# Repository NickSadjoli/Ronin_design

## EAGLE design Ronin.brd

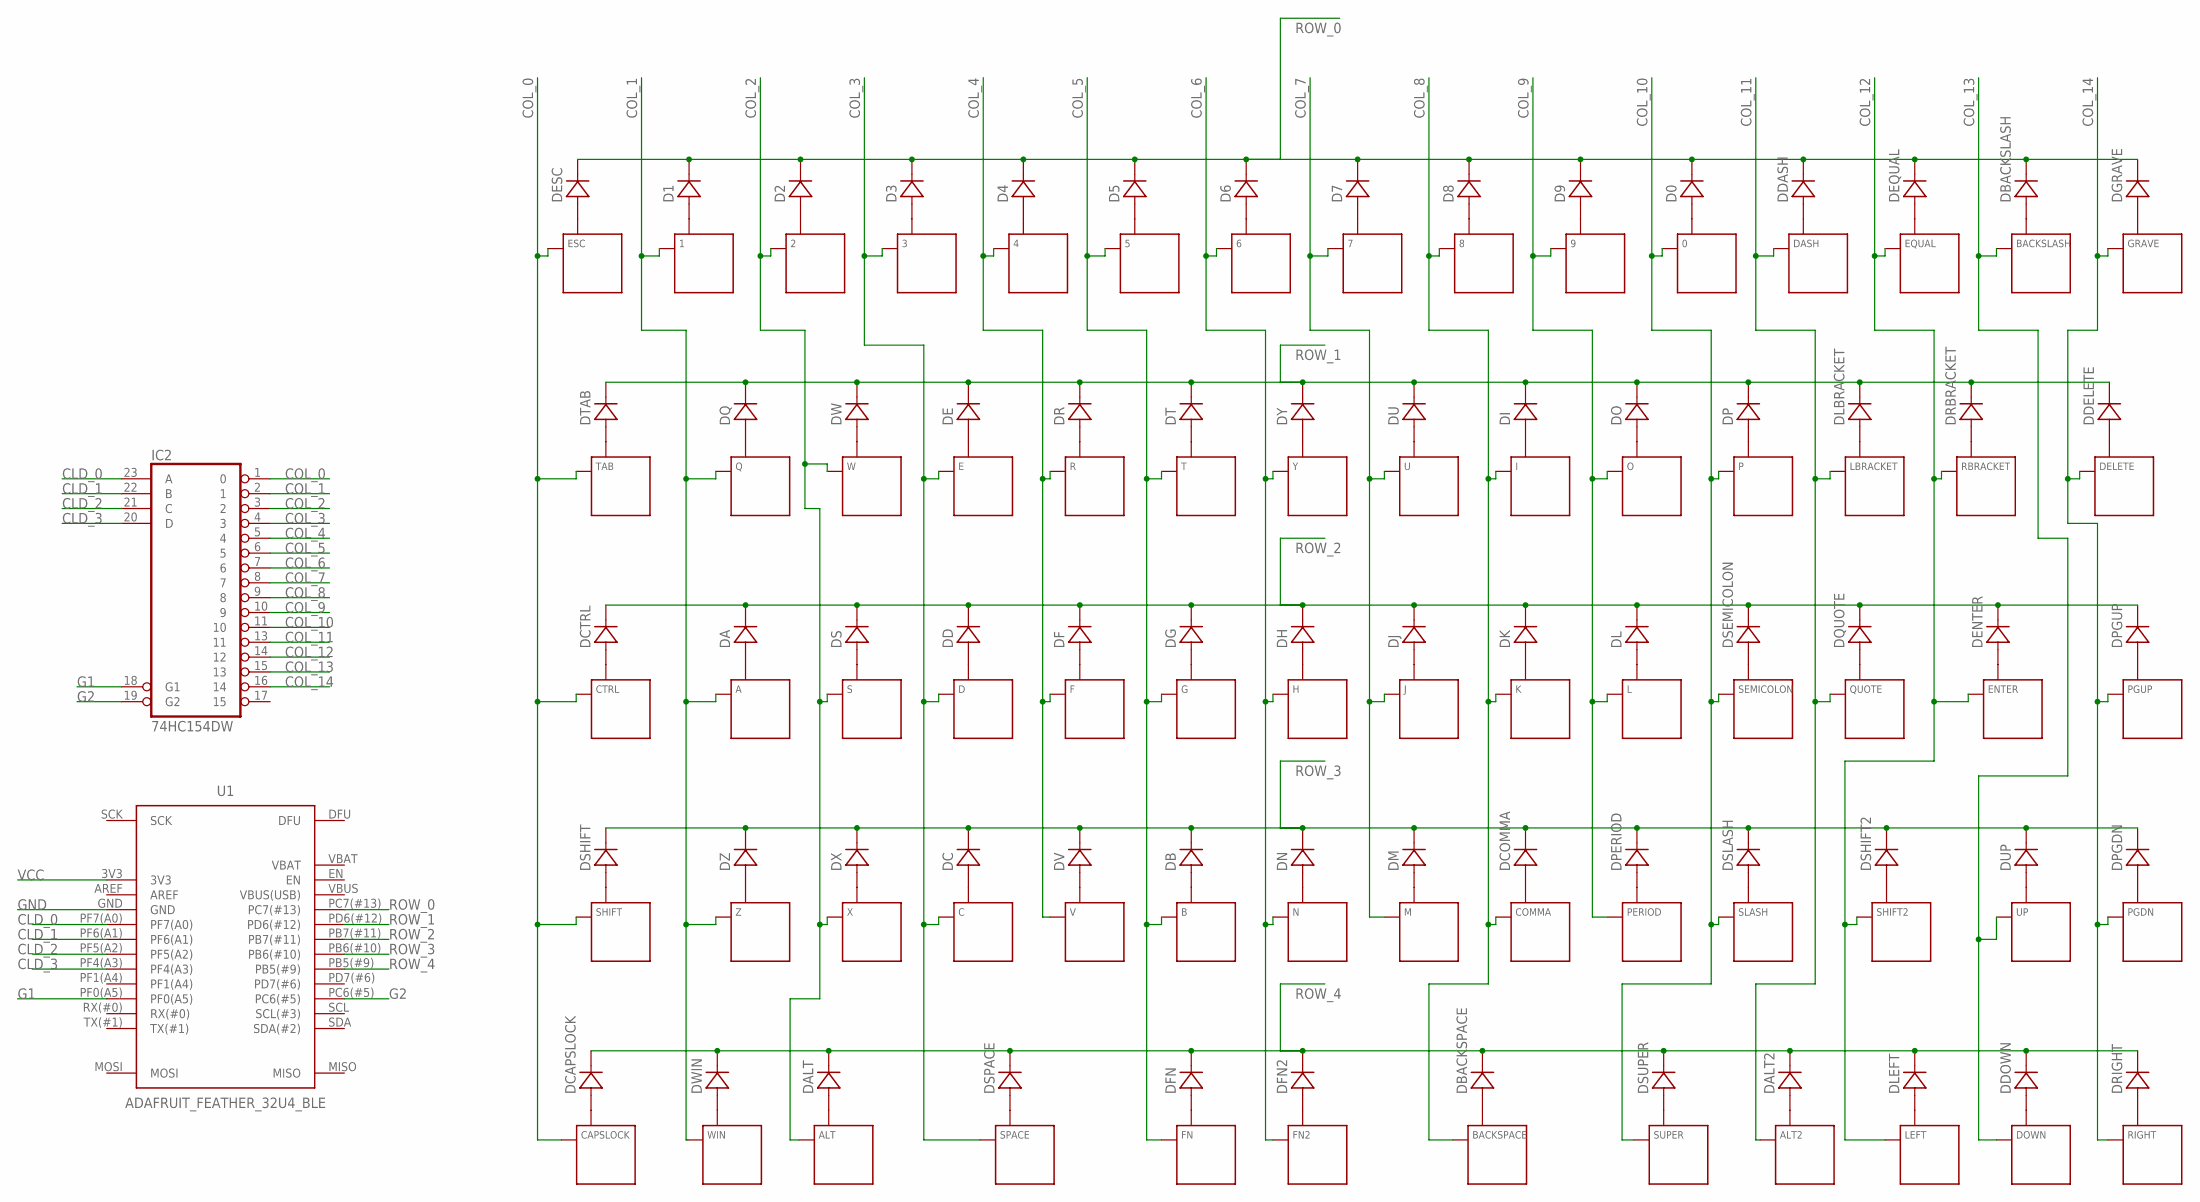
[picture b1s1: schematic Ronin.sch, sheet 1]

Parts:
0, 1, 2, 3, 4, 5, 6, 7, 8, 9: KEYSWITCH-PLAIN-ALPSMX-1U; ALPSMX-1U
A: KEYSWITCH-PLAIN-ALPSMX-1U; ALPSMX-1U
ALT, ALT2: KEYSWITCH-PLAIN-ALPSMX-1U; ALPSMX-1U
B: KEYSWITCH-PLAIN-ALPSMX-1U; ALPSMX-1U
BACKSLASH: KEYSWITCH-PLAIN-ALPSMX-1U; ALPSMX-1U
BACKSPACE: KEYSWITCH-PLAIN-ALPSMX-2U; ALPSMX-2U
C: KEYSWITCH-PLAIN-ALPSMX-1U; ALPSMX-1U
CAPSLOCK: KEYSWITCH-PLAIN-ALPSMX-1U; ALPSMX-1U
COMMA: KEYSWITCH-PLAIN-ALPSMX-1U; ALPSMX-1U
CTRL: KEYSWITCH-PLAIN-ALPSMX-1U; ALPSMX-1U
D: KEYSWITCH-PLAIN-ALPSMX-1U; ALPSMX-1U
D0, D1, D2, D3, D4, D5, D6, D7, D8, D9: DIODE-SOD-123; SOD-123
DA: DIODE-SOD-123; SOD-123
DALT, DALT2: DIODE-SOD-123; SOD-123
DASH: KEYSWITCH-PLAIN-ALPSMX-1U; ALPSMX-1U
DB: DIODE-SOD-123; SOD-123
DBACKSLASH: DIODE-SOD-123; SOD-123
DBACKSPACE: DIODE-SOD-123; SOD-123
DC: DIODE-SOD-123; SOD-123
DCAPSLOCK: DIODE-SOD-123; SOD-123
DCOMMA: DIODE-SOD-123; SOD-123
DCTRL: DIODE-SOD-123; SOD-123
DD: DIODE-SOD-123; SOD-123
DDASH: DIODE-SOD-123; SOD-123
DDELETE: DIODE-SOD-123; SOD-123
DDOWN: DIODE-SOD-123; SOD-123
DE: DIODE-SOD-123; SOD-123
DELETE: KEYSWITCH-PLAIN-ALPSMX-1U; ALPSMX-1U
DENTER: DIODE-SOD-123; SOD-123
DEQUAL: DIODE-SOD-123; SOD-123
DESC: DIODE-SOD-123; SOD-123
DF: DIODE-SOD-123; SOD-123
DFN, DFN2: DIODE-SOD-123; SOD-123
DG: DIODE-SOD-123; SOD-123
DGRAVE: DIODE-SOD-123; SOD-123
DH: DIODE-SOD-123; SOD-123
DI: DIODE-SOD-123; SOD-123
DJ: DIODE-SOD-123; SOD-123
DK: DIODE-SOD-123; SOD-123
DL: DIODE-SOD-123; SOD-123
DLBRACKET: DIODE-SOD-123; SOD-123
DLEFT: DIODE-SOD-123; SOD-123
DM: DIODE-SOD-123; SOD-123
DN: DIODE-SOD-123; SOD-123
DO: DIODE-SOD-123; SOD-123
DOWN: KEYSWITCH-PLAIN-ALPSMX-1U; ALPSMX-1U
DP: DIODE-SOD-123; SOD-123
DPERIOD: DIODE-SOD-123; SOD-123
DPGDN: DIODE-SOD-123; SOD-123
DPGUP: DIODE-SOD-123; SOD-123
DQ: DIODE-SOD-123; SOD-123
DQUOTE: DIODE-SOD-123; SOD-123
DR: DIODE-SOD-123; SOD-123
DRBRACKET: DIODE-SOD-123; SOD-123
DRIGHT: DIODE-SOD-123; SOD-123
DS: DIODE-SOD-123; SOD-123
DSEMICOLON: DIODE-SOD-123; SOD-123
DSHIFT, DSHIFT2: DIODE-SOD-123; SOD-123
DSLASH: DIODE-SOD-123; SOD-123
DSPACE: DIODE-SOD-123; SOD-123
DSUPER: DIODE-SOD-123; SOD-123
DT: DIODE-SOD-123; SOD-123
DTAB: DIODE-SOD-123; SOD-123
DU: DIODE-SOD-123; SOD-123
DUP: DIODE-SOD-123; SOD-123
DV: DIODE-SOD-123; SOD-123
DW: DIODE-SOD-123; SOD-123
DWIN: DIODE-SOD-123; SOD-123
DX: DIODE-SOD-123; SOD-123
DY: DIODE-SOD-123; SOD-123
DZ: DIODE-SOD-123; SOD-123
E: KEYSWITCH-PLAIN-ALPSMX-1U; ALPSMX-1U
ENTER: KEYSWITCH-PLAIN-ALPSMX-1U; ALPSMX-1U
EQUAL: KEYSWITCH-PLAIN-ALPSMX-1U; ALPSMX-1U
ESC: KEYSWITCH-PLAIN-ALPSMX-1U; ALPSMX-1U
F: KEYSWITCH-PLAIN-ALPSMX-1U; ALPSMX-1U
FN, FN2: KEYSWITCH-PLAIN-ALPSMX-1U; ALPSMX-1U
G: KEYSWITCH-PLAIN-ALPSMX-1U; ALPSMX-1U
GRAVE: KEYSWITCH-PLAIN-ALPSMX-1U; ALPSMX-1U
H: KEYSWITCH-PLAIN-ALPSMX-1U; ALPSMX-1U
I: KEYSWITCH-PLAIN-ALPSMX-1U; ALPSMX-1U
IC2: 74HC154DW; SO24W
J: KEYSWITCH-PLAIN-ALPSMX-1U; ALPSMX-1U
K: KEYSWITCH-PLAIN-ALPSMX-1U; ALPSMX-1U
L: KEYSWITCH-PLAIN-ALPSMX-1U; ALPSMX-1U
LBRACKET: KEYSWITCH-PLAIN-ALPSMX-1U; ALPSMX-1U
LEFT: KEYSWITCH-PLAIN-ALPSMX-1U; ALPSMX-1U
M: KEYSWITCH-PLAIN-ALPSMX-1U; ALPSMX-1U
N: KEYSWITCH-PLAIN-ALPSMX-1U; ALPSMX-1U
O: KEYSWITCH-PLAIN-ALPSMX-1U; ALPSMX-1U
P: KEYSWITCH-PLAIN-ALPSMX-1U; ALPSMX-1U
PERIOD: KEYSWITCH-PLAIN-ALPSMX-1U; ALPSMX-1U
PGDN: KEYSWITCH-PLAIN-ALPSMX-1U; ALPSMX-1U
PGUP: KEYSWITCH-PLAIN-ALPSMX-1U; ALPSMX-1U
Q: KEYSWITCH-PLAIN-ALPSMX-1U; ALPSMX-1U
QUOTE: KEYSWITCH-PLAIN-ALPSMX-1U; ALPSMX-1U
R: KEYSWITCH-PLAIN-ALPSMX-1U; ALPSMX-1U
RBRACKET: KEYSWITCH-PLAIN-ALPSMX-1U; ALPSMX-1U
RIGHT: KEYSWITCH-PLAIN-ALPSMX-1U; ALPSMX-1U
S: KEYSWITCH-PLAIN-ALPSMX-1U; ALPSMX-1U
SEMICOLON: KEYSWITCH-PLAIN-ALPSMX-1U; ALPSMX-1U
SHIFT, SHIFT2: KEYSWITCH-PLAIN-ALPSMX-1U; ALPSMX-1U
SLASH: KEYSWITCH-PLAIN-ALPSMX-1U; ALPSMX-1U
SPACE: KEYSWITCH-PLAIN-ALPSMX-2U; ALPSMX-2U
SUPER: KEYSWITCH-PLAIN-ALPSMX-1U; ALPSMX-1U
T: KEYSWITCH-PLAIN-ALPSMX-1U; ALPSMX-1U
TAB: KEYSWITCH-PLAIN-ALPSMX-1U; ALPSMX-1U
U: KEYSWITCH-PLAIN-ALPSMX-1U; ALPSMX-1U
U1: ADAFRUIT_FEATHER_32U4_BLE; ADAFRUIT_FEATHER_32U4_BLUEFRUIT
UP: KEYSWITCH-PLAIN-ALPSMX-1U; ALPSMX-1U
V: KEYSWITCH-PLAIN-ALPSMX-1U; ALPSMX-1U
W: KEYSWITCH-PLAIN-ALPSMX-1U; ALPSMX-1U
WIN: KEYSWITCH-PLAIN-ALPSMX-1U; ALPSMX-1U
X: KEYSWITCH-PLAIN-ALPSMX-1U; ALPSMX-1U
Y: KEYSWITCH-PLAIN-ALPSMX-1U; ALPSMX-1U
Z: KEYSWITCH-PLAIN-ALPSMX-1U; ALPSMX-1U

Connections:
CLD_0: IC2.23 (A), U1.PF7(A0)
CLD_1: IC2.22 (B), U1.PF6(A1)
CLD_2: IC2.21 (C), U1.PF5(A2)
CLD_3: IC2.20 (D), U1.PF4(A3)
COL_0: CAPSLOCK.ALPS1 (P0), CAPSLOCK.MX1 (P0), CTRL.ALPS1 (P0), CTRL.MX1 (P0), ESC.ALPS1 (P0), ESC.MX1 (P0), IC2.1 (0), SHIFT.ALPS1 (P0), SHIFT.MX1 (P0), TAB.ALPS1 (P0), TAB.MX1 (P0)
COL_1: 1.ALPS1 (P0), 1.MX1 (P0), A.ALPS1 (P0), A.MX1 (P0), IC2.2 (1), Q.ALPS1 (P0), Q.MX1 (P0), WIN.ALPS1 (P0), WIN.MX1 (P0), Z.ALPS1 (P0), Z.MX1 (P0)
COL_2: 2.ALPS1 (P0), 2.MX1 (P0), ALT.ALPS1 (P0), ALT.MX1 (P0), IC2.3 (2), S.ALPS1 (P0), S.MX1 (P0), W.ALPS1 (P0), W.MX1 (P0), X.ALPS1 (P0), X.MX1 (P0)
COL_3: 3.ALPS1 (P0), 3.MX1 (P0), C.ALPS1 (P0), C.MX1 (P0), D.ALPS1 (P0), D.MX1 (P0), E.ALPS1 (P0), E.MX1 (P0), IC2.4 (3), SPACE.ALPS1 (P0), SPACE.MX1 (P0)
COL_4: 4.ALPS1 (P0), 4.MX1 (P0), F.ALPS1 (P0), F.MX1 (P0), IC2.5 (4), R.ALPS1 (P0), R.MX1 (P0), V.ALPS1 (P0), V.MX1 (P0)
COL_5: 5.ALPS1 (P0), 5.MX1 (P0), B.ALPS1 (P0), B.MX1 (P0), FN.ALPS1 (P0), FN.MX1 (P0), G.ALPS1 (P0), G.MX1 (P0), IC2.6 (5), T.ALPS1 (P0), T.MX1 (P0)
COL_6: 6.ALPS1 (P0), 6.MX1 (P0), FN2.ALPS1 (P0), FN2.MX1 (P0), H.ALPS1 (P0), H.MX1 (P0), IC2.7 (6), N.ALPS1 (P0), N.MX1 (P0), Y.ALPS1 (P0), Y.MX1 (P0)
COL_7: 7.ALPS1 (P0), 7.MX1 (P0), IC2.8 (7), J.ALPS1 (P0), J.MX1 (P0), M.ALPS1 (P0), M.MX1 (P0), U.ALPS1 (P0), U.MX1 (P0)
COL_8: 8.ALPS1 (P0), 8.MX1 (P0), BACKSPACE.ALPS1 (P0), BACKSPACE.MX1 (P0), COMMA.ALPS1 (P0), COMMA.MX1 (P0), I.ALPS1 (P0), I.MX1 (P0), IC2.9 (8), K.ALPS1 (P0), K.MX1 (P0)
COL_9: 9.ALPS1 (P0), 9.MX1 (P0), IC2.10 (9), L.ALPS1 (P0), L.MX1 (P0), O.ALPS1 (P0), O.MX1 (P0), PERIOD.ALPS1 (P0), PERIOD.MX1 (P0)
COL_10: 0.ALPS1 (P0), 0.MX1 (P0), IC2.11 (10), P.ALPS1 (P0), P.MX1 (P0), SEMICOLON.ALPS1 (P0), SEMICOLON.MX1 (P0), SLASH.ALPS1 (P0), SLASH.MX1 (P0), SUPER.ALPS1 (P0), SUPER.MX1 (P0)
COL_11: ALT2.ALPS1 (P0), ALT2.MX1 (P0), DASH.ALPS1 (P0), DASH.MX1 (P0), IC2.13 (11), LBRACKET.ALPS1 (P0), LBRACKET.MX1 (P0), QUOTE.ALPS1 (P0), QUOTE.MX1 (P0)
COL_12: ENTER.ALPS1 (P0), ENTER.MX1 (P0), EQUAL.ALPS1 (P0), EQUAL.MX1 (P0), IC2.14 (12), LEFT.ALPS1 (P0), LEFT.MX1 (P0), RBRACKET.ALPS1 (P0), RBRACKET.MX1 (P0), SHIFT2.ALPS1 (P0), SHIFT2.MX1 (P0)
COL_13: BACKSLASH.ALPS1 (P0), BACKSLASH.MX1 (P0), DOWN.ALPS1 (P0), DOWN.MX1 (P0), IC2.15 (13), UP.ALPS1 (P0), UP.MX1 (P0)
COL_14: DELETE.ALPS1 (P0), DELETE.MX1 (P0), GRAVE.ALPS1 (P0), GRAVE.MX1 (P0), IC2.16 (14), PGDN.ALPS1 (P0), PGDN.MX1 (P0), PGUP.ALPS1 (P0), PGUP.MX1 (P0), RIGHT.ALPS1 (P0), RIGHT.MX1 (P0)
G1: IC2.18 (G1), U1.PF0(A5)
G2: IC2.19 (G2), U1.PC6(#5)
GND: IC2.12 (GND), U1.GND
unnamed: DESC.A, ESC.ALPS2 (P1), ESC.MX2 (P1)
unnamed: 1.ALPS2 (P1), 1.MX2 (P1), D1.A
unnamed: 2.ALPS2 (P1), 2.MX2 (P1), D2.A
unnamed: 3.ALPS2 (P1), 3.MX2 (P1), D3.A
unnamed: 4.ALPS2 (P1), 4.MX2 (P1), D4.A
unnamed: 5.ALPS2 (P1), 5.MX2 (P1), D5.A
unnamed: 6.ALPS2 (P1), 6.MX2 (P1), D6.A
unnamed: 7.ALPS2 (P1), 7.MX2 (P1), D7.A
unnamed: 8.ALPS2 (P1), 8.MX2 (P1), D8.A
unnamed: 9.ALPS2 (P1), 9.MX2 (P1), D9.A
unnamed: 0.ALPS2 (P1), 0.MX2 (P1), D0.A
unnamed: DASH.ALPS2 (P1), DASH.MX2 (P1), DDASH.A
unnamed: DEQUAL.A, EQUAL.ALPS2 (P1), EQUAL.MX2 (P1)
unnamed: BACKSLASH.ALPS2 (P1), BACKSLASH.MX2 (P1), DBACKSLASH.A
unnamed: DGRAVE.A, GRAVE.ALPS2 (P1), GRAVE.MX2 (P1)
unnamed: DTAB.A, TAB.ALPS2 (P1), TAB.MX2 (P1)
unnamed: DQ.A, Q.ALPS2 (P1), Q.MX2 (P1)
unnamed: DW.A, W.ALPS2 (P1), W.MX2 (P1)
unnamed: DE.A, E.ALPS2 (P1), E.MX2 (P1)
unnamed: DR.A, R.ALPS2 (P1), R.MX2 (P1)
unnamed: DT.A, T.ALPS2 (P1), T.MX2 (P1)
unnamed: DY.A, Y.ALPS2 (P1), Y.MX2 (P1)
unnamed: DU.A, U.ALPS2 (P1), U.MX2 (P1)
unnamed: DI.A, I.ALPS2 (P1), I.MX2 (P1)
unnamed: DO.A, O.ALPS2 (P1), O.MX2 (P1)
unnamed: DP.A, P.ALPS2 (P1), P.MX2 (P1)
unnamed: DLBRACKET.A, LBRACKET.ALPS2 (P1), LBRACKET.MX2 (P1)
unnamed: DRBRACKET.A, RBRACKET.ALPS2 (P1), RBRACKET.MX2 (P1)
unnamed: DDELETE.A, DELETE.ALPS2 (P1), DELETE.MX2 (P1)
unnamed: CTRL.ALPS2 (P1), CTRL.MX2 (P1), DCTRL.A
unnamed: A.ALPS2 (P1), A.MX2 (P1), DA.A
unnamed: DS.A, S.ALPS2 (P1), S.MX2 (P1)
unnamed: D.ALPS2 (P1), D.MX2 (P1), DD.A
unnamed: DF.A, F.ALPS2 (P1), F.MX2 (P1)
unnamed: DG.A, G.ALPS2 (P1), G.MX2 (P1)
unnamed: DH.A, H.ALPS2 (P1), H.MX2 (P1)
unnamed: DJ.A, J.ALPS2 (P1), J.MX2 (P1)
unnamed: DK.A, K.ALPS2 (P1), K.MX2 (P1)
unnamed: DL.A, L.ALPS2 (P1), L.MX2 (P1)
unnamed: DSEMICOLON.A, SEMICOLON.ALPS2 (P1), SEMICOLON.MX2 (P1)
unnamed: DQUOTE.A, QUOTE.ALPS2 (P1), QUOTE.MX2 (P1)
unnamed: DENTER.A, ENTER.ALPS2 (P1), ENTER.MX2 (P1)
unnamed: DPGUP.A, PGUP.ALPS2 (P1), PGUP.MX2 (P1)
unnamed: DSHIFT.A, SHIFT.ALPS2 (P1), SHIFT.MX2 (P1)
unnamed: DZ.A, Z.ALPS2 (P1), Z.MX2 (P1)
unnamed: DX.A, X.ALPS2 (P1), X.MX2 (P1)
unnamed: C.ALPS2 (P1), C.MX2 (P1), DC.A
unnamed: DV.A, V.ALPS2 (P1), V.MX2 (P1)
unnamed: B.ALPS2 (P1), B.MX2 (P1), DB.A
unnamed: DN.A, N.ALPS2 (P1), N.MX2 (P1)
unnamed: DM.A, M.ALPS2 (P1), M.MX2 (P1)
unnamed: COMMA.ALPS2 (P1), COMMA.MX2 (P1), DCOMMA.A
unnamed: DPERIOD.A, PERIOD.ALPS2 (P1), PERIOD.MX2 (P1)
unnamed: DSLASH.A, SLASH.ALPS2 (P1), SLASH.MX2 (P1)
unnamed: DSHIFT2.A, SHIFT2.ALPS2 (P1), SHIFT2.MX2 (P1)
unnamed: DUP.A, UP.ALPS2 (P1), UP.MX2 (P1)
unnamed: DPGDN.A, PGDN.ALPS2 (P1), PGDN.MX2 (P1)
unnamed: CAPSLOCK.ALPS2 (P1), CAPSLOCK.MX2 (P1), DCAPSLOCK.A
unnamed: DWIN.A, WIN.ALPS2 (P1), WIN.MX2 (P1)
unnamed: ALT.ALPS2 (P1), ALT.MX2 (P1), DALT.A
unnamed: DSPACE.A, SPACE.ALPS2 (P1), SPACE.MX2 (P1)
unnamed: DFN.A, FN.ALPS2 (P1), FN.MX2 (P1)
unnamed: DFN2.A, FN2.ALPS2 (P1), FN2.MX2 (P1)
unnamed: BACKSPACE.ALPS2 (P1), BACKSPACE.MX2 (P1), DBACKSPACE.A
unnamed: DSUPER.A, SUPER.ALPS2 (P1), SUPER.MX2 (P1)
unnamed: ALT2.ALPS2 (P1), ALT2.MX2 (P1), DALT2.A
unnamed: DLEFT.A, LEFT.ALPS2 (P1), LEFT.MX2 (P1)
unnamed: DDOWN.A, DOWN.ALPS2 (P1), DOWN.MX2 (P1)
unnamed: DRIGHT.A, RIGHT.ALPS2 (P1), RIGHT.MX2 (P1)
ROW_0: D0.C, D1.C, D2.C, D3.C, D4.C, D5.C, D6.C, D7.C, D8.C, D9.C, DBACKSLASH.C, DDASH.C, DEQUAL.C, DESC.C, DGRAVE.C, U1.PC7(#13)
ROW_1: DDELETE.C, DE.C, DI.C, DLBRACKET.C, DO.C, DP.C, DQ.C, DR.C, DRBRACKET.C, DT.C, DTAB.C, DU.C, DW.C, DY.C, U1.PD6(#12)
ROW_2: DA.C, DCTRL.C, DD.C, DENTER.C, DF.C, DG.C, DH.C, DJ.C, DK.C, DL.C, DPGUP.C, DQUOTE.C, DS.C, DSEMICOLON.C, U1.PB7(#11)
ROW_3: DB.C, DC.C, DCOMMA.C, DM.C, DN.C, DPERIOD.C, DPGDN.C, DSHIFT.C, DSHIFT2.C, DSLASH.C, DUP.C, DV.C, DX.C, DZ.C, U1.PB6(#10)
ROW_4: DALT.C, DALT2.C, DBACKSPACE.C, DCAPSLOCK.C, DDOWN.C, DFN.C, DFN2.C, DLEFT.C, DRIGHT.C, DSPACE.C, DSUPER.C, DWIN.C, U1.PB5(#9)
VCC: IC2.24 (VCC), U1.3V3

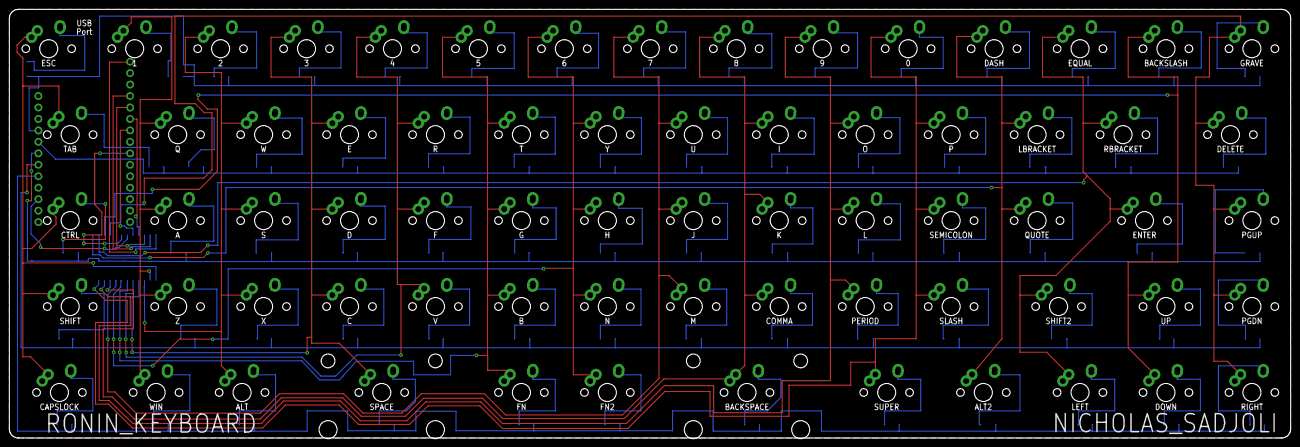
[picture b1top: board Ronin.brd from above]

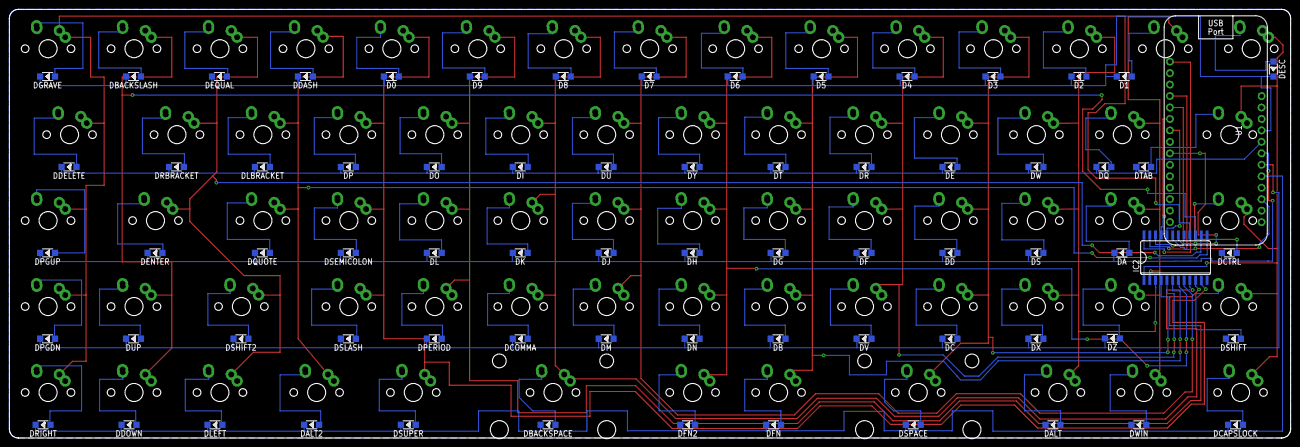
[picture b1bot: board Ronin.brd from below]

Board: 2 copper layers, 284.0 x 95.0 mm, 140 parts (71 on the bottom side), 97 nets.

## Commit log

2017-10-02 EagleCAD Design files for Ronin Keyboard
